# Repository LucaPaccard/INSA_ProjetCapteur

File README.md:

# 2021-2022_Paccard_Lemaire_Projet_Capteur
Ce projet s'inscrit dans l'UF **"Du capteur au banc de test"** en 4ème année au département de Génie Physique de l'INSA Toulouse.
***
L'objectif de ce dernier est d'élaborer un **capteur de déformation** low-tech à base de graphite. L'application d'une contrainte mécanique sur un capteur en papier sur lequel un dépôt de crayon à papier à été fait, modifie la distance entre les particules de graphite. La conductivité électrique de la couche de graphite est elle aussi modifiée et celà induit une variation de la résistance. C'est cette donnée qui va nous intéresser.

<p align="center">

L'ensemble des étapes menées pour réaliser ce capteur, en allant du **design** jusqu'à la **réalisation** en passant par le **codage** seront détaillées dans ce dossier.

## Sommaire
* [1. Description du projet et détail des livrables](#PremiereSection)
* [2. Matériel nécessaire](#DeuxiemeSection)
* [3. Arduino](#TroisiemeSection)
  * [3.1. Librairies utilisées](#TroisiemeSection1)
  * [3.2. Code Arduino](#TroisiemeSection1)
* [4. Application Android](#QuatriemeSection)
* [5. KiCad](#CinquiemeSection)
  * [5.1. Symboles et empreintes des composants](#CinquiemeSection1)
  * [5.2. Schématique](#CinquiemeSection2)
  * [5.3. Placement des composants](#CinquiemeSection3)
  * [5.4. Visualisation 3D](#CinquiemeSection4)
* [6. Fabrication du shield](#SixiemeSection)
  * [6.1. Réalisation du PCB](#SixiemeSection1)
  * [6.2. Perçage et soudure](#SixiemeSection2)
* [7. Simulation](#SeptiemeSection)
* [8. Tests et résultats](#HuigtiemeSection)
  * [8.1. Banc de test](#HuigtiemeSection1)
  * [8.2. Résultats obtenus](#HuigtiemeSection2)
  * [8.3. Analyse des résultats et pistes d'améliorations](#HuigtiemeSection3)
* [9. Datasheet](#NeuviemeSection)
* [Contacts](#DixiemeSection)

## 1. Détail des livrables et description du projet 
Voici l'ensemble des livrables du projet :
- Un **shield PCB** se connectant à une carte **Arduino UNO** contenant un amplificateur transimpédance, un module bluetooth, un écran OLED et un encodeur rotatoire
- Un **code Arduino** permettant de mesurer la déformation du capteur et de piloter le module bluetooth, l'écran OLED et l'encodeur rotatoire
- Une **application Android APK**
- Un **protocole de test** 
- La **datasheet** du capteur de déformation

Tout d'abord, nous avons réalisé un code Arduino permettant de vérifier notre montage contenant un amplificateur transimpédance, un écran OLED, un module bluetooth et un encodeur rotatoire. Une fois le montage fonctionnel, nous avons réalisé le design de notre shield sur le logiciel *KiCad*. Nous l'avons ensuite fabriqué et assemblé (lithographie, perçage, soudage des composants, etc.). En parallèle de cela, nous avons utilisé le logiciel *MIT App Inventor* afin de développer une application Android APK, capable de communiquer et recevoir les informations envoyées par le module bluetooth telles que les valeurs de résistance du capteur mesurées. Nous avons par la suite mis en place un banc de test pour pour caractériser les différents types de capteurs en fonction de leur déformation et de la mine de crayon utilisée (HB, B, 9B, etc.). Enfin, nous avons établi une datasheet à l'aide des résulats obtenus par le banc de test.

## 2. Matériel nécessaire
Pour réaliser le capteur ainsi que le PCB associé, voici la liste des composants nécessaires :
* x2 résistance 100kΩ
* x1 résistance 10kΩ
* x2 résistance 1kΩ
* x1 capacité 1μF
* x3 capacité 100nF
* x1 amplificateur opérationnel LTC1050
* x1 module Bluetooth HC05
* x1 encodeur rotatoire KY_040
* x1 écran OLED I2C 0.91

## 3. Arduino 
### 3.1. Librairies utilisées 
Nous avons utilisé différentes librairies dans notre code Arduino. La librarie ["Adafruit_SSD1306"](/Libraries/Adafruit_SSD1306) permet de contrôller l'écran OLED. La librairie ["Adafruit_BusIO"](/Libraries/Adafruit_busIO) permet de gérer la connexion en I2C et SPI.

### 3.2. Code Arduino 
[Deux codes Arduino](https://github.com/MOSH-Insa-Toulouse/2021-2022_Paccard_Lemaire_Projet_Capteur/tree/main/Arduino) ont été développés sous Arduino IDE pour profiter au mieux des fonctionnalités de notre capteur.

#### Code Graphite_sensor
Le [premier code](https://github.com/MOSH-Insa-Toulouse/2021-2022_Paccard_Lemaire_Projet_Capteur/blob/main/Arduino/Graphite_sensor/Graphite_sensor.ino) permet d'assurer la communication entre la carte Arduino, qui récupère la valeur de tension renvoyée par le capteur, et les différents éléments ajoutés sur le shield soit : l'écran OLED, le module bluetooth et l'encodeur rotatoire. Différents menus sont accessibles sur l'écran OLED :
* Le premier menu permet un simple affichage de la résistance
* Le deuxième menu permet de selectionner le calibre de la résistance affichée sur le menu 1. Cette dernière peut ainsi être affichée en Ω, kΩ ou MΩ.
* Le troisème menu est un chronomètre permettant de savoir le temps d'execution du programme. C'est à dire le temps depuis le programme à été démarré.
* Le quatrième menu permet l'affichage d'une image.

En parallèle, le module bluetooth envoie les données de tension et de résistance à une application mobile qui sera détaillée dans la partie suivante.

#### Code Angle_calibration
Le [second code](https://github.com/MOSH-Insa-Toulouse/2021-2022_Paccard_Lemaire_Projet_Capteur/blob/main/Arduino/Angle_calibration/Angle_calibration.ino) Arduino permet d'effectuer un calcul d'angle par rapport à la calibration du capteur. L'utilisateur rentre les valeurs de la résistance à plat et à la position la plus courbée possible en appuyant sur le bouton poussoir présent sur l'encodeur rotatoire. En considérant la variation de résistance linéaire, un produit en croix est ensuite fait pour asssocier une valeur de résistance à un angle de déformation.

## 4. Application Android 

Nous avons réalisé une [application Android](https://github.com/MOSH-Insa-Toulouse/2021-2022_Paccard_Lemaire_Projet_Capteur/tree/main/Application%20bluetooth) grâce au site *MIT App Inventor* afin d'instaurer une communication entre notre module bluetooth HC-05 et un smartphone Android. Cette application possède différentes fonctionnalités : après avoir choisi dans un menu l'appareil auquel on souhaite se connecter, et que la connexion a été effectuée, différentes informations sont affichées sur l'écran du téléphone. En premier, on trouve la tension VADC en volts de sortie du circuit, elle est envoyée sous forme d'un byte à l'application depuis la carte Arduino, puis elle est reconvertie dans le code de l'application en float permettant d'afficher les décimales. C'est ensuite la valeur de la résistance du capteur en graphite qui est affichée en Méga Ohms, la valeur est directement calculée depuis l'application à partir de la valeur de VADC reconvertie en float. Finalement, la variation de la valeur de résistance est tracée en fonction du temps dans un graphique (canva) au-dessous. Nous avons enregistré un graphique avec uniquement des axes et leurs titres sous forme d'image que nous avons ensuite mis en fond du graphique pour le tracé. 

## 5. KiCad 
### 5.1. Symboles et empreintes des composants 
* Amplificateur LTC1050

* Ecran OLED

* Encodeur rotatoire KY_040

* Module bluetooth HC05

### 5.2. Schématique 
<p align="center">

Une fois les empreintes créées, nous avons réalisé le schéma de notre shield. En haut à droite sont représentées les broches de la carte Arduino. En haut au milieu est représenté l'amplificateur transimpédance et en bas du schématique se trouvent l'écran OLED, le module bluetooth et l'encodeur rotatoire.

### 5.3. Placement des composants 
<p align="center">

### 5.4. Visualisation 3D 
<p align="center">

## 6. Fabrication du shield 

### 6.1. Réalisation du PCB  
Le PCB a été réalisé au sein des départements de Génie Physique (GP) et Génie Électrique et Informatique (GEI) de l'INSA Toulouse avec l'aide de Catherine Crouzet. Notre PCB à été fabriqué à partir d'une plaquette d'epoxy recouverte d'une fine couche de cuivre (environ 60μm). 
Nous avons imprimé sur du papier calque la modélisation de notre PCB effectuée sur le logiciel *KICAD* pour ensuite insoler aux UV notre plaquette avec la silouhette par-dessus pendant quelques minutes. À l'aide d'un révelateur, nous avons retiré la partie de la résine non insolée.
La plaquette d'expoxy est ensuite placée dans un bain de perchlorure de fer pour la gravure, opération durant 7 minutes. Le cuivre non protégé par la résine est ainsi retiré de la plaquette ce qui nous permet d'obtenir le PCB avec les pistes souhaitées.
Enfin, de l'acétone est appliquée sur la plaquette pour éliminer les dernières traces de résine.

### 6.2. Perçage et soudure  
Nous avons ensuite percé notre PCB aux endroits où les différents composants seront insérés à l'aide d'une perceuse électrique. Le diamètre des trous dépend des différents composants à placer :
* ⌀ 0.8mm : AOP LTC1050, résistances et capacités
* ⌀ 1.0mm : Broches de connexion de la carte Arduino Uno et headers des différents modules (OLED, bluetooth, encodeur rotatoire)
* ⌀ 1.2mm : Broches de connexion du capteur de déformation

Notre PCB ayant été imprimé en face avant, certains composants ont été placé en face avant et d'autres en face arrière pour faciliter la soudure et la connexion à la carte Arduino Uno.

## 7. Simulation  
Nous avons simulé notre amplificateur transimpédance sur le logiciel *LTSpice* afin de savoir le comportement que notre circuit aura une fois branché à de réelles valeurs de tension. Les différentes simulations réalisées sur le logiciel nous ont permis d'une part de vérifier le bon fonctionnement du circuit et de chacun des composants intégrés, et d'autre part de comprendre l'utilité de chacun. Le détail de la démarche suivie et des résultats obtenus est disponible dans le document [Simulation_LTspice](https://github.com/MOSH-Insa-Toulouse/2021-2022_Paccard_Lemaire_Projet_Capteur/blob/main/Simulation_LTspice.pdf).

## 8. Tests et résultats  
### 8.1. Banc de test  
<p align="center">

Nous avons testé notre capteur sur un banc de test que nous avons conçu à partir de feuilles de papier épais. Nous avons fabriqué 7 cylindres de diamètre variable, allant de 5cm à 2cm par pas de 0,5cm.
En enrobant les différents cylindres avec notre capteur, nous appliquons une déformation maitrisée que nous pouvons calculer avec la formule : 
*ε = e / (2•R)*, avec ε la déformation, e l'épaisseur de notre capteur, et R le rayon de courbure appliqué soit le rayon de nos cylindres.

Nous avons décidé de réaliser des mesures de compression (graphite vers le cylindre) du capteur et pas en tension (graphite vers l'extérieur), car bien que ces deux méthodes soient possibles, les valeurs de  résistance renvoyées par notre capteur en tension n'étaient pas exploitables.

### 8.2. Résultats obtenus  
Les résultats complets de notre banc de test sont disponibles dans le dossier [Results](https://github.com/MOSH-Insa-Toulouse/2021-2022_Paccard_Lemaire_Projet_Capteur/tree/main/Results). 

### 8.3. Analyse des résultats et pistes d'améliorations  
En comprimant notre capteur, les particules de graphite se rapprochent les unes des autres, ce qui facilite la conduction dans le réseau percolé du système. De la même manière, en mettant notre capteur en tension, certains chemins de percolation se retrouvent brisés ce qui augmente la résistance du capteur.
En fonction du type de crayon utilisé, les variations relatives de résistance changent. En effet, plus le crayon est gras, c'est à dire qu'il dépose plus de graphite, moins sa variation relative de résistance est élevée. Cette caractéristique se vérifie sur nos [résultats](https://github.com/MOSH-Insa-Toulouse/2021-2022_Paccard_Lemaire_Projet_Capteur/tree/main/Results) et dans notre [datasheet](https://github.com/MOSH-Insa-Toulouse/2021-2022_Paccard_Lemaire_Projet_Capteur/blob/main/datasheet.pdf).
 
#### Comparaison avec le Flex-Sensor SEN-10264

 <p align="center">  
 <p align="center">
 
Nous avons étudié la réponse en résistance du flex-sensor SEN-10264 pour le comparer à nos capteurs low-tech à base de graphite. Nous avons observé que le flex-sensor industriel est plus sensible à la déformation (i.e. ΔR/R0 augmente plus rapidement avec la déformation) que nos capteurs de graphite lorsque l'on applique une déformation en tension. Cependant, en compression, le flex-sensor SEN-10264 possède une sensibilité du même ordre de grandeur que nos différents capteurs.
 
#### Pistes d'améliorations 
Certains point peuvent être améliorés dans notre projet :
* Le dépot de graphite sur le capteur est difficile à maîtriser et il est ainsi difficile de fabriquer plusieurs capteurs identiques
* Notre banc de test fourni des résultats répétables, il pourrait cependant être envisageable de fabriquer ce même banc de test en impression 3D pour augmenter sa résistance et longévitée.
* Sur notre PCB, l'ajout d'un potentiomètre digital permettrait de pouvoir travailler sur une gamme de résistance plus grande car ce dernier modulera la valeur de tension de sortie en fonction de la résistance du capteur

## 9. Datasheet  
La datasheet de notre capteur est disponible [ici](https://github.com/MOSH-Insa-Toulouse/2021-2022_Paccard_Lemaire_Projet_Capteur/blob/main/datasheet.pdf).

## Contacts  
Pour toutes questions relatives aux différentes parties du projet, que ce soit du KiCad au code Arduino, n'hésitez pas à nous contacter !
* Luca Paccard : paccard@insa-toulouse.fr
* Arthur Lemaire : a_lemair@insa-toulouse.fr

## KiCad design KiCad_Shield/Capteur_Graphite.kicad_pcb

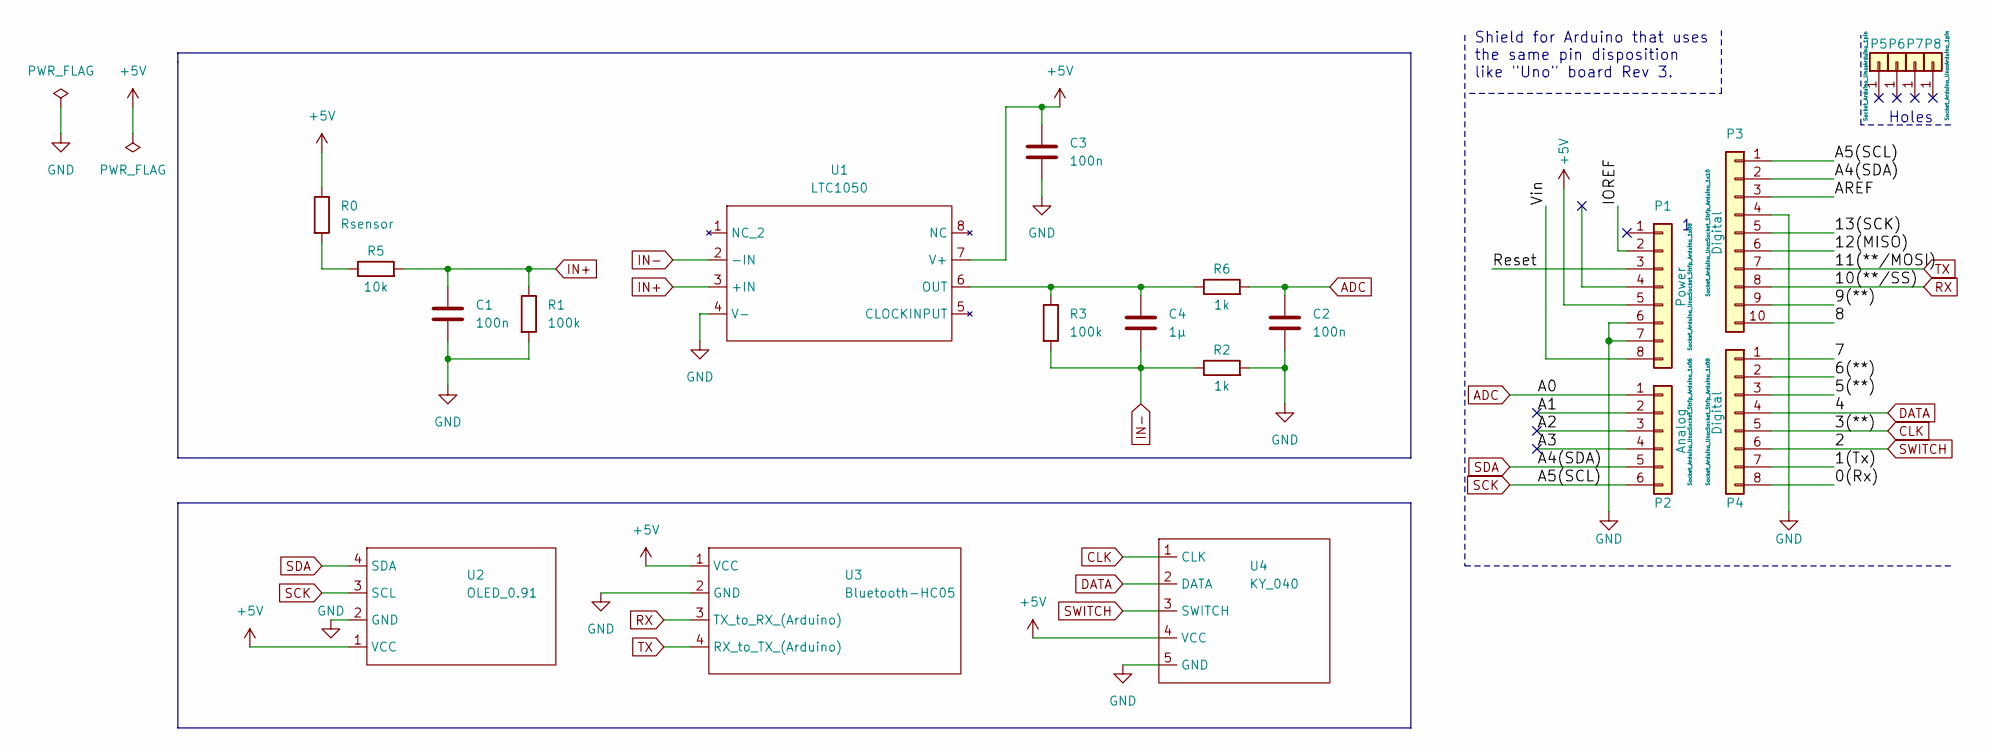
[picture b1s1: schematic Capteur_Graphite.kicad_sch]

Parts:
C1, C2, C3: 100n; C_Rect_L7.0mm_W2.0mm_P5.00mm
C4: 1µ; C_Rect_L7.0mm_W2.0mm_P5.00mm
P1: Power; Socket_Strip_Arduino_1x08
P2: Analog; Socket_Strip_Arduino_1x06
P3: Digital; Socket_Strip_Arduino_1x10
P4: Digital; Socket_Strip_Arduino_1x08
P5, P6, P7, P8: CONN_01X01; Arduino_1pin
R0: Rsensor; R_Axial_DIN0207_L6.3mm_D2.5mm_P7.62mm_Horizontal
R1, R3: 100k; R_Axial_DIN0207_L6.3mm_D2.5mm_P7.62mm_Horizontal
R2: 1k; R_Axial_DIN0204_L3.6mm_D1.6mm_P7.62mm_Horizontal
R5: 10k; R_Axial_DIN0207_L6.3mm_D2.5mm_P7.62mm_Horizontal
R6: 1k; R_Axial_DIN0204_L3.6mm_D1.6mm_P5.08mm_Horizontal
U1: LTC1050
U2: OLED_0.91; OLED
U3: Bluetooth-HC05; Bluetooth_HC05
U4: KY_040

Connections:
+5V: C3.1, P1.5, R0.1, U1.7 (V+), U2.1 (VCC), U3.1 (VCC), U4.4 (VCC)
/0(Rx): P4.8
/1(Tx): P4.7
/5(**): P4.3
/6(**): P4.2
/7: P4.1
/8: P3.10
/9(**): P3.9
/12(MISO): P3.6
/13(SCK): P3.5
/A1: P2.2
/A2: P2.3
/A3: P2.4
/AREF: P3.3
/IOREF: P1.2
/Reset: P1.3
/Vin: P1.8
ADC: C2.1, P2.1, R6.2
CLK: P4.5, U4.1 (CLK)
DATA: P4.4, U4.2 (DATA)
GND: C1.2, C2.2, C3.2, P1.6, P1.7, P3.4, R1.2, R2.2, U1.4 (V-), U2.2 (GND), U3.2 (GND), U4.5 (GND)
IN+: C1.1, R1.1, R5.2, U1.3 (+IN)
IN-: C4.2, R2.1, R3.2, U1.2 (-IN)
unnamed: C4.1, R3.1, R6.1, U1.6 (OUT)
unnamed: R0.2, R5.1
RX: P3.8, U3.3 (TX_to_RX_(Arduino))
SCK: P2.6, P3.1, U2.3 (SCL)
SDA: P2.5, P3.2, U2.4 (SDA)
SWITCH: P4.6, U4.3 (SWITCH)
TX: P3.7, U3.4 (RX_to_TX_(Arduino))

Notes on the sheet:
Holes
Shield for Arduino that uses the same pin disposition like "Uno" board Rev 3.

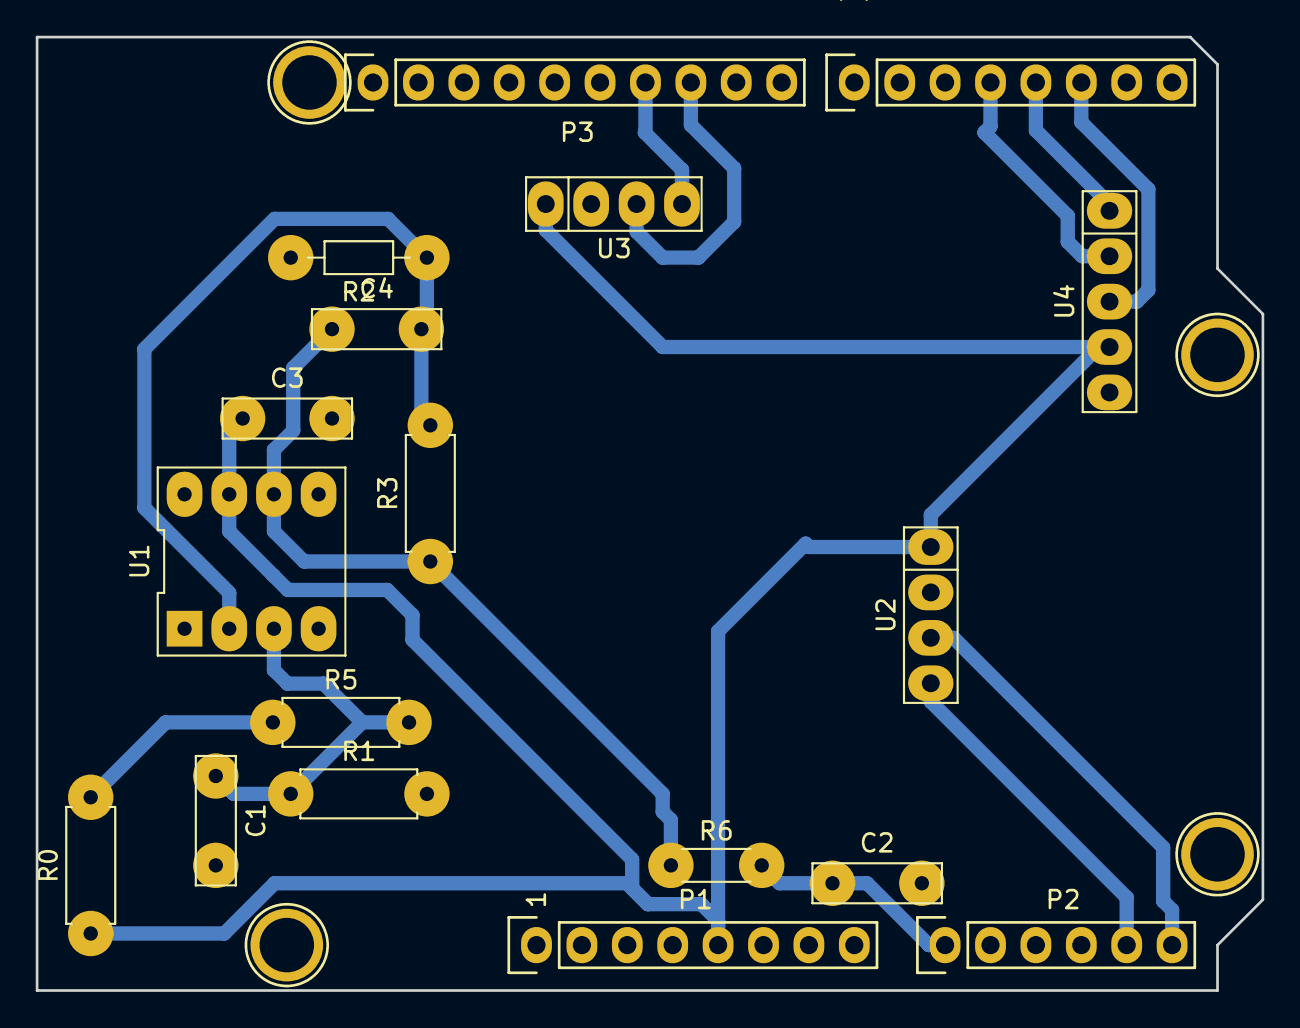
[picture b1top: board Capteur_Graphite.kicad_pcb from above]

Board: 2 copper layers, 68.6 x 53.3 mm, 22 parts (0 on the bottom side), 14 nets.

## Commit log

2022-04-11 Create oui
2022-04-11 README.md
2022-04-11 Test
2022-04-11 Libraries
2022-04-11 Images
2022-04-12 Add of Schematique_globale.png
2022-04-12 Add of PCB
2022-04-12 add of PCB photos
2022-04-12 Add capteur
2022-04-12 Shield KiCad
2022-04-14 Add test bench image
2022-04-14 add bench test image
2022-04-14 Arduino code
2022-04-14 update angle_calibration
2022-04-15 Add bench test results
2022-04-15 Add datasheet v1
2022-04-19 Final bench test results
2022-04-19 Minor graph title change
2022-04-19 datasheet
2022-04-19 bluetooth correction
2022-04-20 update nbre de chiffres significatifs
2022-04-22 Create Analyse_Resultats
2022-04-22 Ajout des data du flex sensor
